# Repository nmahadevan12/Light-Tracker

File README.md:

# 2-Axis Light Tracker

A battery-powered dual-axis light tracker on an ATmega328P. Bare-metal C drives DC motors through MOSFET H-bridges, with LDR sensing, fixed-point Kalman filtering, Hall-effect tilt limits, and UART telemetry to a Python logger.

## Demo

[YouTube short](https://www.youtube.com/shorts/PQEl34fqnAk)

## Features

- **Bare-metal dual-axis drive:** ATmega328P C firmware driving motors with MOSFET H-bridges.
- **Tilt safety:** LDR array with Hall-effect and potentiometer feedback to keep tilt within safe limits.
- **Fixed-point Kalman + UART:** cuts ADC noise from 3 LSBs to < 1 LSB without an FPU; streams results over a register-level 115.2 kbps UART driver.
- **4-layer KiCad PCB:** separate power, ground, and signal layers; widened power traces to reduce voltage drop.

## Repo layout

```text
.
├── ATmega328P Datasheet/
├── Images/
├── Kicad Files/          # Schematics + PCB
├── src/
│   ├── IoT Logging/      # Python UART logger (folder name is historical)
│   └── Source Code/      # AVR C firmware
└── README.md
```

## More detail

Design notes, gallery, and interactive PCB: [nmahadevan12.github.io/projects/light-tracker/](https://nmahadevan12.github.io/projects/light-tracker/)

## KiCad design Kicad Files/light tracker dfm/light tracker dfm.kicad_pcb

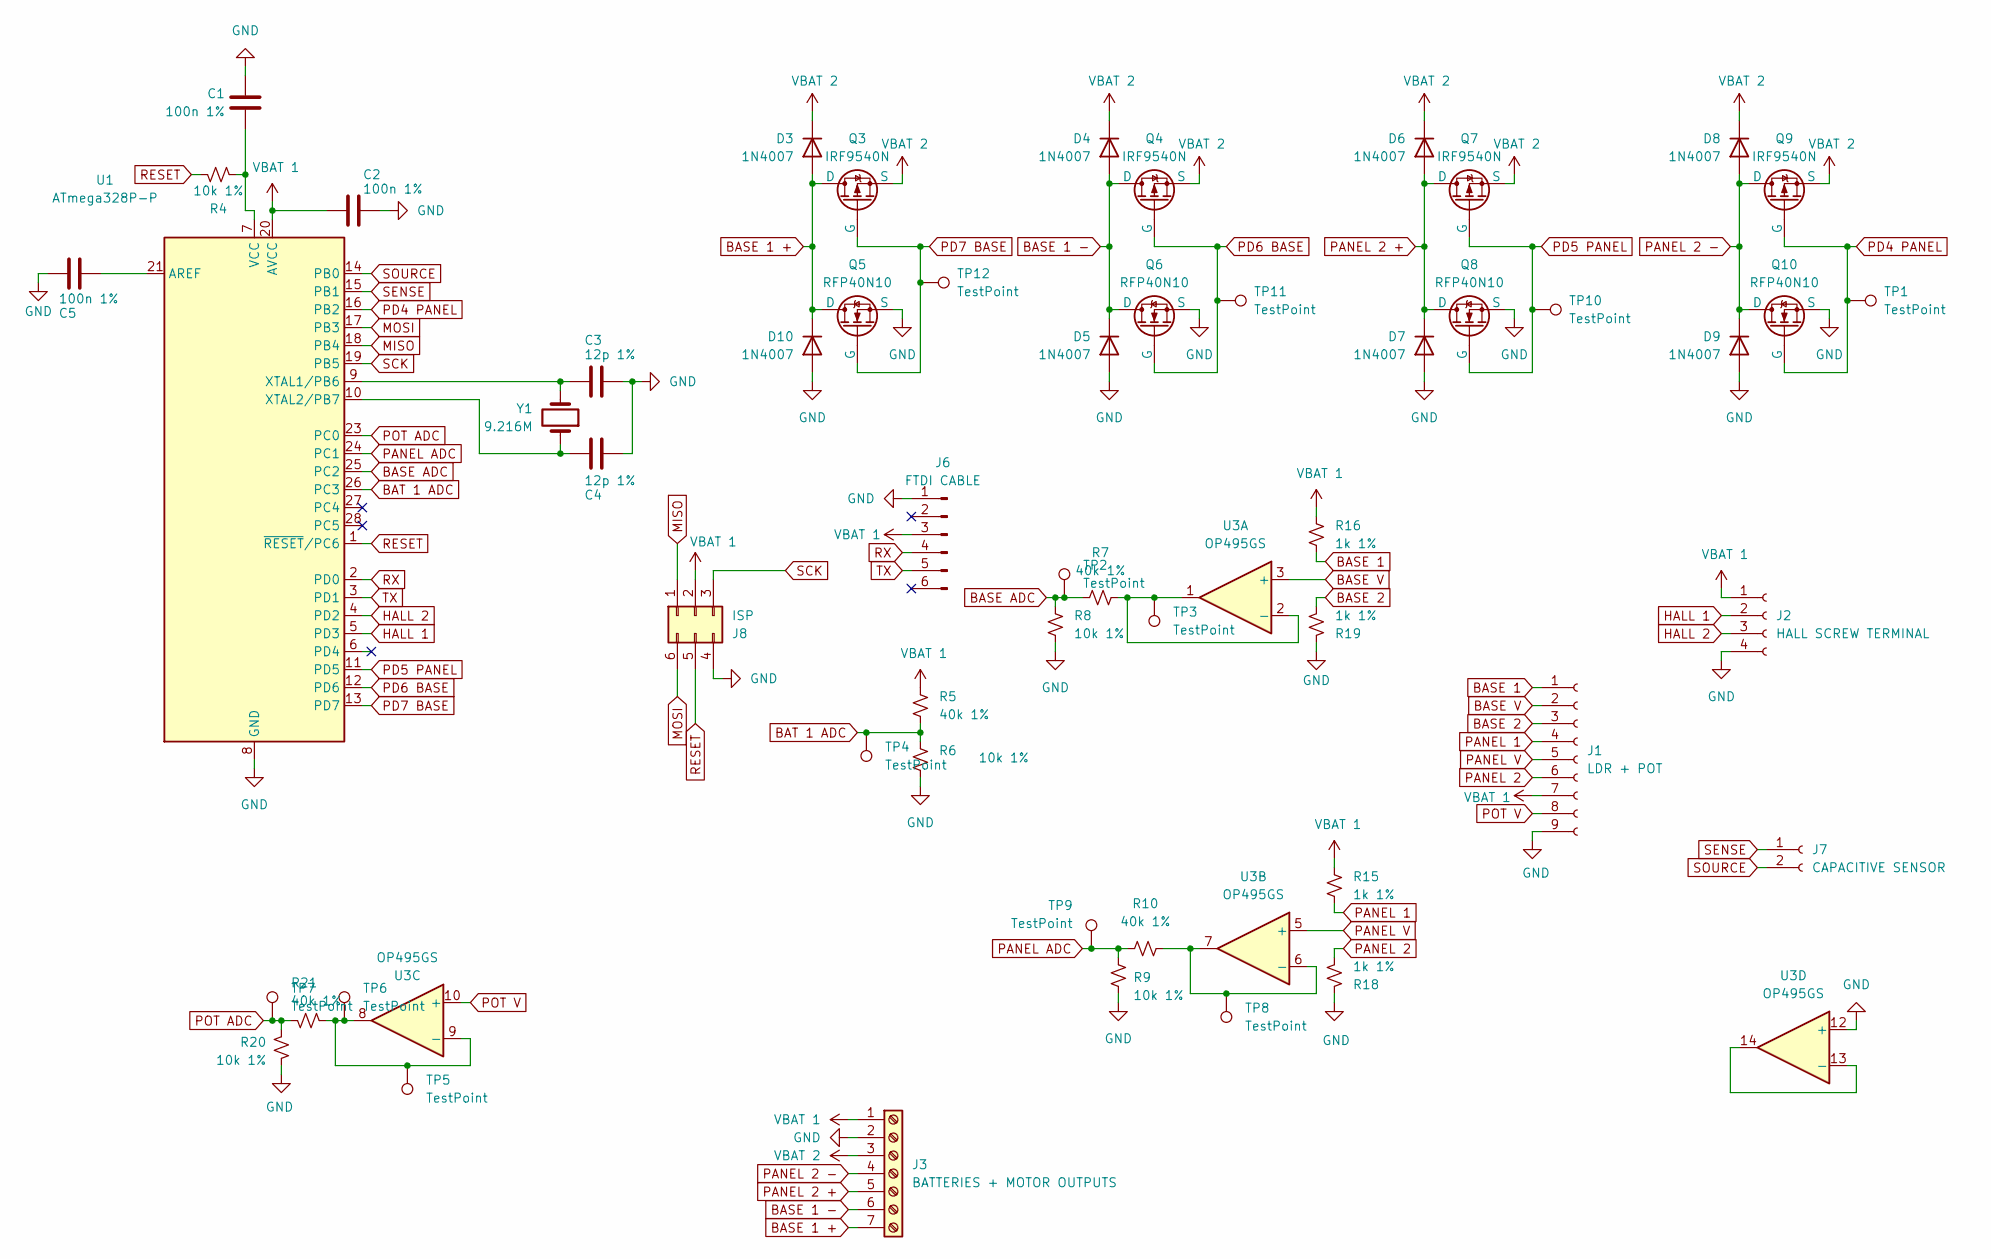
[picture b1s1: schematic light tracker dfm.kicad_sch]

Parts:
C1, C2, C5: 100n 1%; C_0805_2012Metric
C3, C4: 12p 1%; C_0805_2012Metric
D3, D4, D5, D6, D7, D8, D9, D10: 1N4007; D_DO-41_SOD81_P2.54mm_Vertical_AnodeUp
J1: LDR + POT; PinSocket_1x09_P2.54mm_Vertical
J2: HALL SCREW TERMINAL; PinSocket_1x04_P2.54mm_Vertical
J3: BATTERIES + MOTOR OUTPUTS; TerminalBlock_Phoenix_MKDS-1,5-7-5.08_1x07_P5.08mm_Horizont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
J6: FTDI CABLE; PinHeader_1x06_P2.54mm_Vertical
J7: CAPACITIVE SENSOR; PinSocket_1x02_P2.54mm_Vertical
J8: ISP; PinHeader_2x03_P2.54mm_Vertical
Q3, Q4, Q7, Q9: IRF9540N; TO-220-3_Vertical
Q5, Q6, Q8, Q10: RFP40N10; TO-220-3_Vertical
R4, R6, R8, R9, R20: 10k 1%; R_0805_2012Metric
R5, R7, R10, R21: 40k 1%; R_0805_2012Metric
R15, R16, R18, R19: 1k 1%; R_0805_2012Metric
TP1, TP2, TP3, TP4, TP5, TP6, TP7, TP8, TP9, TP10, TP11, TP12: TestPoint; TestPoint_Pad_1.0x1.0mm
U1: ATmega328P-P; DIP-28_W7.62mm_LongPads
U3: OP495GS; SOIC-16W_7.5x10.3mm_P1.27mm
Y1: 9.216M; Crystal_SMD_5032-2Pin_5.0x3.2mm

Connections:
BASE 1: J1.1, R16.1
BASE 1 +: D3.2 (A), D10.1 (K), J3.7, Q3.2 (D), Q5.2 (D)
BASE 1 -: D4.2 (A), D5.1 (K), J3.6, Q4.2 (D), Q6.2 (D)
BASE 2: J1.3, R19.1
BASE ADC: R7.1, R8.2, TP2.1 (1_1), U1.25 (PC2)
BASE V: J1.2, U3.3 (+)
BAT 1 ADC: R5.1, R6.2, TP4.1 (1_1), U1.26 (PC3)
GND: C1.1, C2.2, C3.2, C4.2, C5.1, D5.2 (A), D7.2 (A), D9.2 (A), D10.2 (A), J1.9, J2.4, J3.2, J6.1, J8.4, Q5.3 (S), Q6.3 (S), Q8.3 (S), Q10.3 (S), R6.1, R8.1, R9.1, R18.2, R19.2, R20.1, U1.8 (GND), U1.22 (GND), U3.11 (V-), U3.12 (+)
HALL 1: J2.2, U1.5 (PD3)
HALL 2: J2.3, U1.4 (PD2)
MISO: J8.1, U1.18 (PB4)
MOSI: J8.6, U1.17 (PB3)
unnamed: C5.2, U1.21 (AREF)
unnamed: C1.2, R4.1, U1.7 (VCC)
unnamed: C3.1, U1.9 (XTAL1/PB6), Y1.2
unnamed: C4.1, U1.10 (XTAL2/PB7), Y1.1
unnamed: R7.2, TP3.1 (1_1), U3.1, U3.2 (-)
unnamed: R10.2, TP8.1 (1_1), U3.6 (-), U3.7
unnamed: R21.2, TP5.1 (1_1), TP6.1, U3.8, U3.9 (-)
unnamed: U3.13 (-), U3.14
PANEL 1: J1.4, R15.1
PANEL 2: J1.6, R18.1
PANEL 2 +: D6.2 (A), D7.1 (K), J3.5, Q7.2 (D), Q8.2 (D)
PANEL 2 -: D8.2 (A), D9.1 (K), J3.4, Q9.2 (D), Q10.2 (D)
PANEL ADC: R9.2, R10.1, TP9.1 (1_1), U1.24 (PC1)
PANEL V: J1.5, U3.5 (+)
PD4 PANEL: Q9.1 (G), Q10.1 (G), TP1.1 (1_1), U1.16 (PB2)
PD5 PANEL: Q7.1 (G), Q8.1 (G), TP10.1 (1_1), U1.11 (PD5)
PD6 BASE: Q4.1 (G), Q6.1 (G), TP11.1 (1_1), U1.12 (PD6)
PD7 BASE: Q3.1 (G), Q5.1 (G), TP12.1 (1_1), U1.13 (PD7)
POT ADC: R20.2, R21.1, TP7.1 (1_1), U1.23 (PC0)
POT V: J1.8, U3.10 (+)
RESET: J8.5, R4.2, U1.1 (~RESET/PC6)
RX: J6.4, U1.2 (PD0)
SCK: J8.3, U1.19 (PB5)
SENSE: J7.1, U1.15 (PB1)
SOURCE: J7.2, U1.14 (PB0)
TX: J6.5, U1.3 (PD1)
VBAT 1: C2.1, J1.7, J2.1, J3.1, J6.3, J8.2, R5.2, R15.2, R16.2, U1.20 (AVCC), U3.4 (V+)
VBAT 2: D3.1 (K), D4.1 (K), D6.1 (K), D8.1 (K), J3.3, Q3.3 (S), Q4.3 (S), Q7.3 (S), Q9.3 (S)

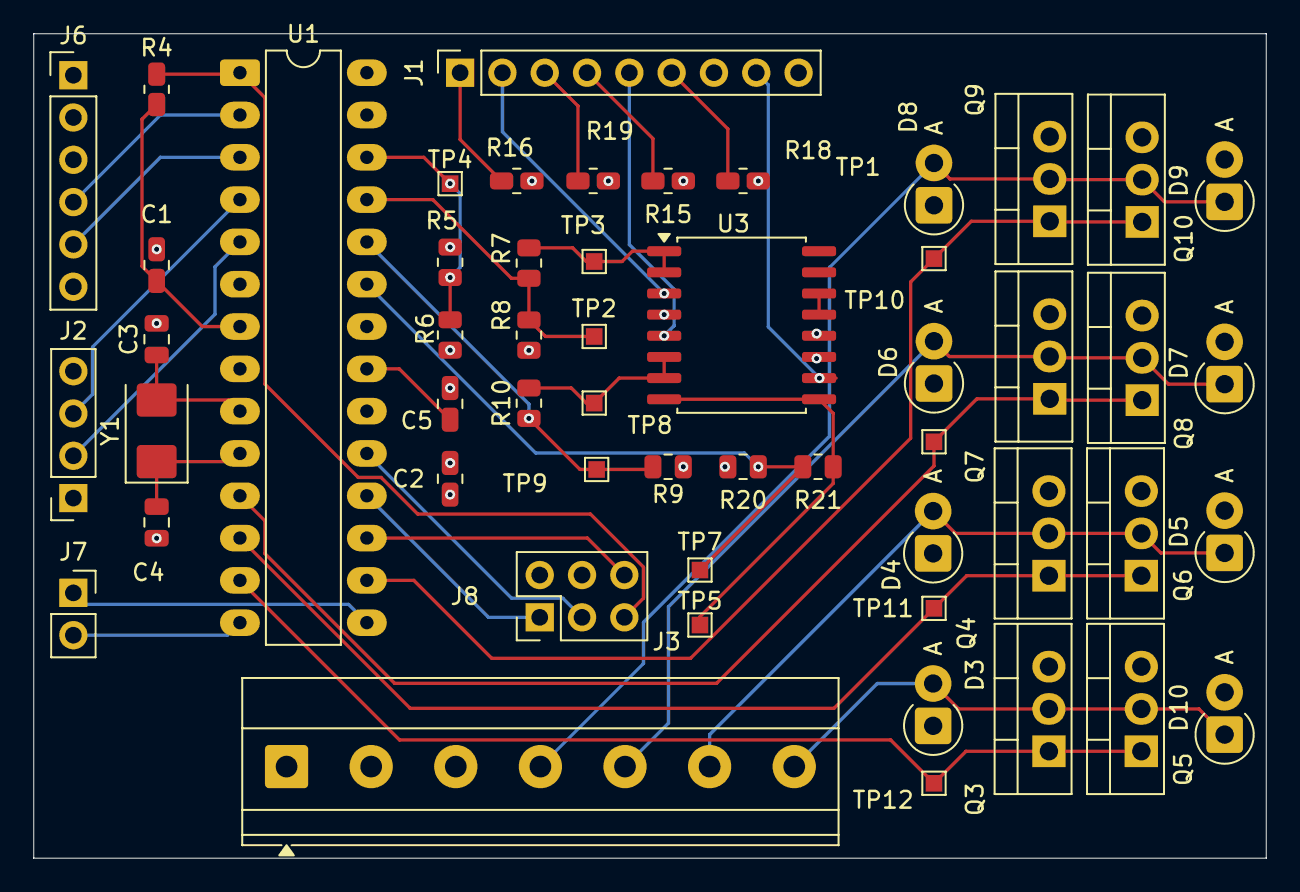
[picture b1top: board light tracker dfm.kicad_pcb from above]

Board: 4 copper layers, 74.0 x 49.5 mm, 54 parts (0 on the bottom side), 40 nets.

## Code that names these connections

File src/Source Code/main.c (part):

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#define MOTOR_OFF           0x00 // 0b00000000

#define BASE_MOTOR_RESET    0x3F // 0b00111111
#define BASE_MOTOR_CW       0x80 // 0b10000000 (PD7)
#define BASE_MOTOR_CCW      0x40 // 0b01000000 (PD6)
#define BASE_MOTOR_MASK     0xC0 // 0b11000000

#define PANEL_MOTOR_RESET   0xCF // 0b11001111
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#define TX                  (1 << TXEN0)
#define BAUD_RATE           9

// Capacitive touch sensor pins: SEND = Arduino pin 8 (PB0), RECEIVE = Arduino pin 12 (PB4)
#define SEND_OUTPUT          (1 << PB0) // 0b00000001
#define RECEIVE_PULL_UP_OFF  ~(1 << PB4) // 0b11101111
#define RECEIVE_PIN          (1 << PB4) // 0b00010000

char sprint_buf[128];

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    DDRD |= MOTOR_OUTPUTS;
}

// Configures PD2 (right hall) and PD3 (left hall) as inputs
void inputPin(void)
{
    DDRD &= ~(1 << DDD2);
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
    // ** ONLY ENABLED ONCE ON BOOT

    // Capacitive touch check (SEND = PB0 / Arduino pin 8, RECEIVE = PB4 / Arduino pin 12)
    unsigned int touch_time = 0;

    DDRB = (DDRB & 0b11101110) | SEND_OUTPUT; // Reset PB0 (SEND) PB4 (RECEIVE); set send = 1 (OUTPUT)
    PORTB &= RECEIVE_PULL_UP_OFF; // Set RECEIVE pull-up LOW

    DDRB |= RECEIVE_PIN; // Set RECEIVE to OUTPUT
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        ///////////////////////////////////
        /////// Hall Effect Check /////////
        ///////////////////////////////////
        uint8_t right_hall_high = (PIND >> 2) & 1; // PD2 (Right)
        uint8_t left_hall_high  = (PIND >> 3) & 1; // PD3 (Left)

        if (right_hall_high)
        {
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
